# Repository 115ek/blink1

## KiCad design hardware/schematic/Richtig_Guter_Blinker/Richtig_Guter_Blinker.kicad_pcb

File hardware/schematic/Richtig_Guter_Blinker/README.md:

# Richtig Guter Blinker
*Richtig Guter Blinker*  is a blink(1) mk2 clone with focus on simplicity and compactness thought to be assembled at home. It uses the same hardware components but differs in following points:
- smaller size: 16 x 28 mm compared to 35 x 36 mm of a blink(1) mk2
- parts chosen for easy hand-soldering
  - 0805 packages (capacitors, resistor)
  - microcontroller in SOIC-14 package (1.27 mm pitch)
- USB connector directly on PCB safes costs and reduces size
- lead through ICSP contacts (2.54 mm pinheader) for easy programming
  - programming also possible with not mounting pinheader to keep size low
  - just use male connector and tilt it

### TODO
- USB bootloader to allow firmware updates without extra programmer
- case / LED diffusor (maybe 3D printing?)

### Status
- 10 prototypes assembled
- PCB thickness of 1.6 mm is not sufficient for USB connector (2.4 mm ?)
- USB connector pads should get ENIG surface finish to  improve durability
- problems with some WS2812B LEDs encountered (cheap clones?)
  - solved by using LEDs from other supplier

### Pictures

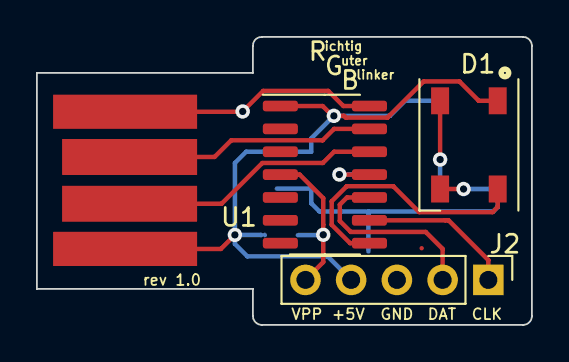
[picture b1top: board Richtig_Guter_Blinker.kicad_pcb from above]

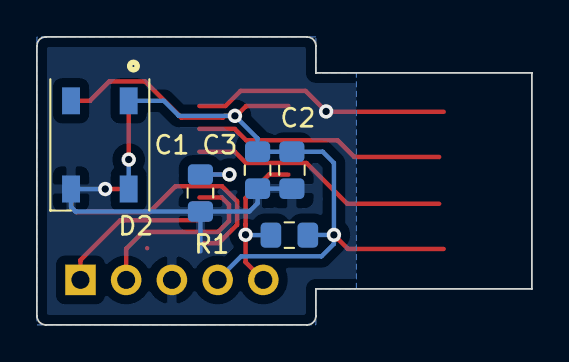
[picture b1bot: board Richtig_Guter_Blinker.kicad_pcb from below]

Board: 2 copper layers, 27.5 x 16.0 mm, 9 parts (5 on the bottom side), 10 nets.

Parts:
C1, C3: 100nF; C_0805_2012Metric_Pad1.15x1.40mm_HandSolder
C2: 10uF; C_0805_2012Metric_Pad1.15x1.40mm_HandSolder
D1, D2: WS2812B; LED_WS2812B_PLCC4_5.0x5.0mm_P3.2mm
J1: USB_A; usb-PCB
J2: Conn_01x05_Male; PinHeader_1x05_P2.54mm_Vertical
R1: 10k; R_0805_2012Metric_Pad1.15x1.40mm_HandSolder
U1: PIC16F1455-ISL; SOIC-14_3.9x8.7mm_P1.27mm

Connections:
+5V: C2.1, C3.1, D1.1, D2.1, J1.1, J2.4, R1.2, U1.1
D+: J1.3, U1.13
D-: J1.2, U1.12
DI: D1.4, U1.8
GND: C1.2, C2.2, C3.2, D1.3, D2.3, J1.4, J2.3, U1.14
ICSPCLK: J2.1, U1.9
ICSPDAT: J2.2, U1.10
unnamed: C1.1, U1.11
unnamed: D1.2, D2.4
VPP: J2.5, R1.1, U1.4

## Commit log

2019-05-07 add modified pcb
2019-05-07 add some pictures
